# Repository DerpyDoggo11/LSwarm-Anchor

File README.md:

# LSwarm Anchor
A UWB Anchor made for the LSwarm micro drones

## 3D Preview

## Wiring

## Schematic

### Download ./latestProduction to begin fabricating the PCB

## Introduction
In an effort to make a cheaper alternative for micro drones, specifically for volumetric (3D) light displays, I designed drones that use an ultra-wide-band (UWB) module instead of an expensive gps to communicate with ground stations with UWB modules often called anchors. With three of these modules placed in a triangular formation, you can estimate the drone's specific position in 2D space. With four or more of these modules, you can precisely track the drone's position in a full 3D space. I recommend around 5 modules for more precision (also LCSC tends to offer pcbs in terms of 5 which makes this almost just as cheap), but four modules will work as well. 

I have not physically tested this device yet, but typically UWB modules can have a range of up to 100 meters or around 300 feet, which is more than enough for many applications. Also, UWB frequenceis can work through walls, but it may be less accurate or cause desyncing with the drone. 

Note: These anchors do not actively run the computations to position the drones, you must also have a dedicated ground station with wifi such as a Raspbbery PI Zero 2 W for computing.

## Bill of Materials (for 5 anchors)

| Quantity | Components | Price | Link |
|--------- |----------|----------| -----|
| 5  | 18650 Batteries | ~$33.93 (with shipping) | [here](https://liionwholesale.com/products/molicel-npe-inr-18650-m35a-10a-3500mah-flat-top-18650-battery-authorized-distributor?variant=32004772528197)
| 5 | 2.4G Wifi Antenna | ~$1.39 | select 5cm FPC-IPX4 cable from [here](https://www.aliexpress.us/item/3256802833801038.html?spm=a2g0o.productlist.main.17.44bbCrBdCrBdFl&algo_pvid=20d56933-2b0c-45d5-8601-1bc6a9682401&algo_exp_id=20d56933-2b0c-45d5-8601-1bc6a9682401-16&pdp_ext_f=%7B%22order%22%3A%221074%22%2C%22eval%22%3A%221%22%2C%22fromPage%22%3A%22search%22%7D&pdp_npi=6%40dis%21USD%213.55%213.52%21%21%213.55%213.52%21%402101ef5e17781321493642302e40a6%2112000023272348781%21sea%21US%217493938711%21X%211%210%21n_tag%3A-29913%3Bd%3A21b1ce8d%3Bm03_new_user%3A-29895&curPageLogUid=rLnZuf4b98Bi&utparam-url=scene%3Asearch%7Cquery_from%3A%7Cx_object_id%3A1005003020115790%7C_p_origin_prod%3A)
| 5  | LS Anchor PCBs | ~$10 (with shipping, cost can vary widely however) | Download repo, extract fabrication files, and fabricate through JLCPCB (complete instructions for this may come soon)
| 5  | Electrical Components for each PCB | ~$88.67 (this is on the high end, cost can vary widely) | See production BOM for a full list, the PCB fabrication files automatically include these components as well.
Total: $133.99

## Tools / Other parts:
- Hot-air reflow station or SMD hot plate
- Soldering iron + solder
- Solder paste for SMD components
- Tweezers for SMD components

For drone light displays, you'll also need the drones and a ground station.

## Assembly:
1. Apply solder paste to all smd components directly or through a stencil
2. Heat up components with a hot plate or hot-air gun
3. Solder on the battery connector and connect the battery
4. Plug in USB-C port and upload software

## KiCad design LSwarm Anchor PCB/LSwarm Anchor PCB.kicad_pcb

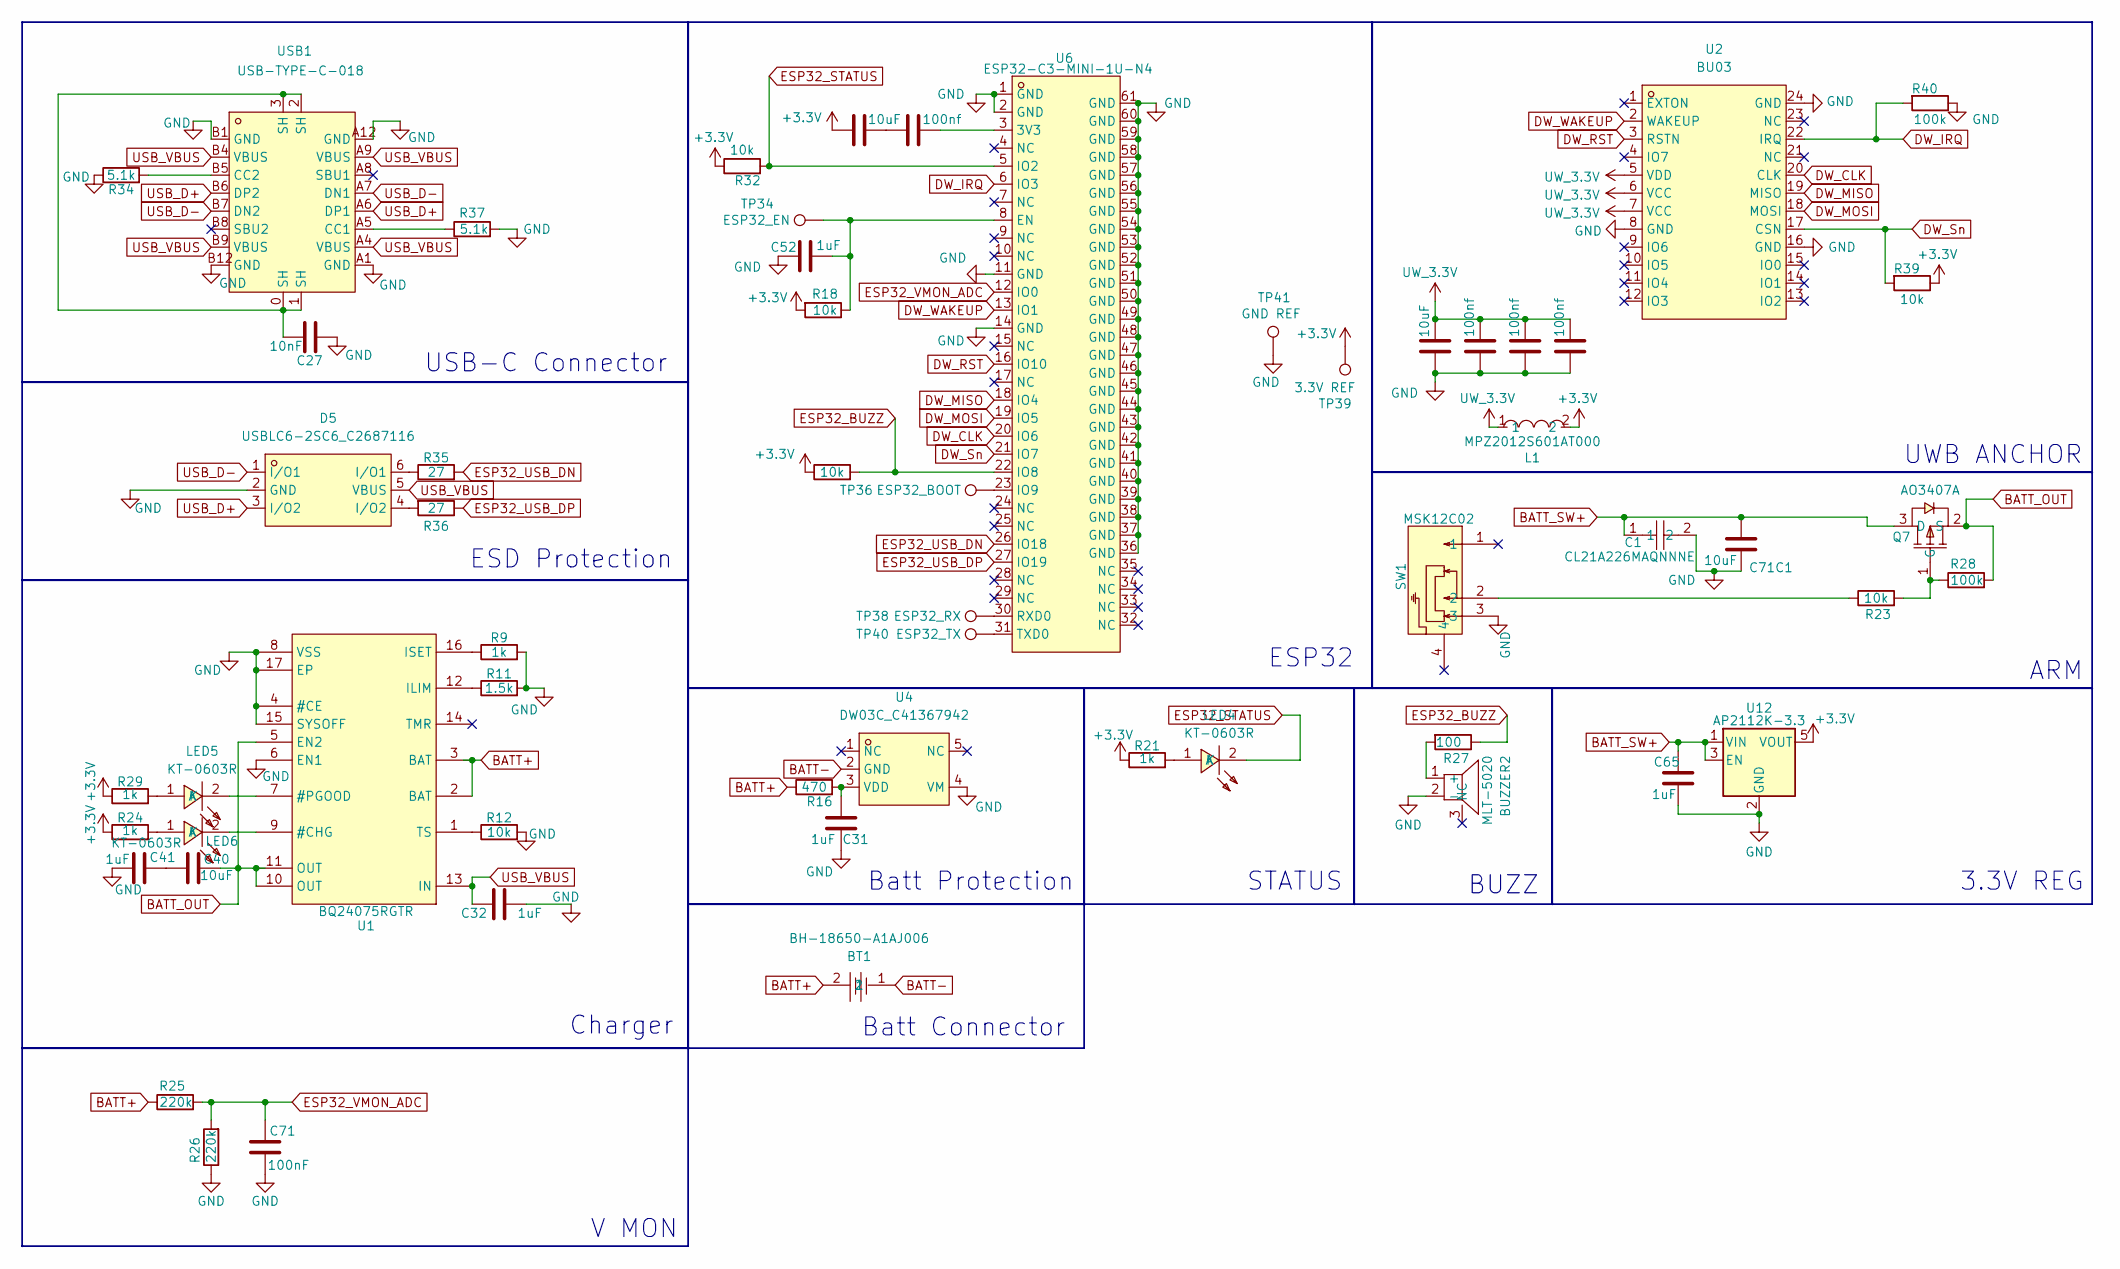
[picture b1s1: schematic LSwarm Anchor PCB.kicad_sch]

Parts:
BT1: BH-18650-A1AJ006; BAT-TH_BH-18650-A1AJ006; MPN BH-18650-A1AJ006; LCSC Part C5290175
BUZZER2: MLT-5020; BUZ-SMD_L5.0-W5.5-P4.60; MPN MLT-5020; LCSC Part C94598
C1: CL21A226MAQNNNE; C0805; MPN CL21A226MAQNNNE; LCSC Part C45783
C27: 10nF; C_0603_1608Metric
C31, C32, C41, C52, C65: 1uF; C_0603_1608Metric
C40, C55, C62: 10uF; C_0603_1608Metric
C56, C58, C59, C61: 100nf; C_0603_1608Metric
C71: 100nF; C_0603_1608Metric
C71C1: 10uF; C_0805_2012Metric
D5: USBLC6-2SC6_C2687116; SOT-23-6_L2.9-W1.6-P0.95-LS2.8-BL; MPN USBLC6-2SC6; LCSC Part C2687116
L1: MPZ2012S601AT000; L0805; MPN MPZ2012S601AT000; LCSC Part C21519
LED4, LED5, LED6: KT-0603R; LED-SMD_L1.6-W0.8-R-RD; MPN KT-0603R; LCSC Part C2286
Q7: AO3407A; SOT-23-3_L2.9-W1.6-P1.90-LS2.8-BR; MPN AO3407A; LCSC Part C15155
R9, R21, R24, R29: 1k; R_0603_1608Metric
R11: 1.5k; R_0603_1608Metric
R12, R18, R23, R32, R33, R39: 10k; R_0603_1608Metric
R16: 470; R_0603_1608Metric
R25, R26: 220k; R_0603_1608Metric
R27: 100; R_0603_1608Metric
R28, R40: 100k; R_0603_1608Metric
R34, R37: 5.1k; R_0603_1608Metric
R35, R36: 27; R_0603_1608Metric
SW1: MSK12C02; SW-TH_MSK12C02; MPN MSK12C02; LCSC Part C431540
TP34: ESP32_EN; TestPoint_Pad_1.0x1.0mm
TP36: ESP32_BOOT; TestPoint_Pad_1.0x1.0mm
TP38: ESP32_RX; TestPoint_Pad_1.0x1.0mm
TP39: 3.3V REF; TestPoint_Pad_1.0x1.0mm
TP40: ESP32_TX; TestPoint_Pad_1.0x1.0mm
TP41: GND REF; TestPoint_Pad_1.0x1.0mm
U1: BQ24075RGTR; QFN-16_L3.0-W3.0-P0.50-TL-EP1.7; MPN BQ24075RGTR; LCSC Part C15464
U2: BU03; WIRELM-SMD_BU03; MPN BU03; LCSC Part C42419011
U4: DW03C_C41367942; SOT-23-5_L2.9-W1.6-P0.95-LS2.9-BL; MPN DW03C; LCSC Part C41367942
U6: ESP32-C3-MINI-1U-N4; WIFIM-SMD_61P-L13.2-W12.5-P0.80; MPN ESP32-C3-MINI-1U-N4; LCSC Part C2911374
U12: AP2112K-3.3; SOT-23-5
USB1: USB-TYPE-C-018; USB-C_SMD-TYPE-C-31-M-12; MPN USB-TYPE-C-018; LCSC Part C2927038

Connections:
+3.3V: C55.2, L1.2, R18.2, R21.1, R24.1, R29.1, R32.1, R33.1, R39.1, TP39.1 (1_1), U12.5 (VOUT)
BATT+: BT1.2, R16.1, R25.1, U1.2 (BAT), U1.3 (BAT)
BATT-: BT1.1, U4.2 (GND)
BATT_OUT: C40.1, Q7.2 (S), R28.2, U1.5 (EN2), U1.10 (OUT), U1.11 (OUT)
BATT_SW+: C1.1, C65.2, C71C1.2, Q7.3 (D), U12.1 (VIN), U12.3 (EN)
DW_CLK: U2.20 (CLK), U6.20 (IO6)
DW_IRQ: R40.2, U2.22 (IRQ), U6.6 (IO3)
DW_MISO: U2.19 (MISO), U6.18 (IO4)
DW_MOSI: U2.18 (MOSI), U6.19 (IO5)
DW_RST: U2.3 (RSTN), U6.16 (IO10)
DW_Sn: R39.2, U2.17 (CSN), U6.21 (IO7)
DW_WAKEUP: U2.2 (WAKEUP), U6.13 (IO1)
ESP32_BUZZ: R27.1, R33.2, U6.22 (IO8)
ESP32_STATUS: LED4.2 (K), R32.2, U6.5 (IO2)
ESP32_USB_DN: R35.2, U6.26 (IO18)
ESP32_USB_DP: R36.1, U6.27 (IO19)
ESP32_VMON_ADC: C71.2, R25.2, R26.2, U6.12 (IO0)
GND: BUZZER2.2 (-), C1.2, C27.1, C31.2, C32.1, C41.1, C52.1, C58.2, C59.2, C61.2, C62.2, C65.1, C71.1, C71C1.1, D5.2 (GND), R9.2, R11.2, R12.2, R26.1, R34.1, R37.2, R40.1, SW1.3, TP41.1 (1_1), U1.4 (#CE), U1.6 (EN1), U1.8 (VSS), U1.15 (SYSOFF), U1.17 (EP), U2.8 (GND), U2.16 (GND), U2.24 (GND), U4.4 (VM), U6.1 (GND), U6.2 (GND), U6.11 (GND), U6.14 (GND), U6.36 (GND), U6.37 (GND), U6.38 (GND), U6.39 (GND), U6.40 (GND), U6.41 (GND), U6.42 (GND), U6.43 (GND), U6.44 (GND), U6.45 (GND), U6.46 (GND), U6.47 (GND), U6.48 (GND), U6.49 (GND), U6.50 (GND), U6.51 (GND), U6.52 (GND), U6.53 (GND), U6.54 (GND), U6.55 (GND), U6.56 (GND), U6.57 (GND), U6.58 (GND), U6.59 (GND), U6.60 (GND), U6.61 (GND), U12.2 (GND), USB1.A1 (GND), USB1.A12 (GND), USB1.B1 (GND), USB1.B12 (GND)
unnamed: BUZZER2.1 (+), R27.2
unnamed: C27.2, USB1.0 (SH), USB1.1 (SH), USB1.2 (SH), USB1.3 (SH)
unnamed: C40.2, C41.2
unnamed: C55.1, C56.2
unnamed: D5.6 (I/O1), R35.1
unnamed: D5.4 (I/O2), R36.2
unnamed: LED4.1 (A), R21.2
unnamed: LED5.1 (A), R29.2
unnamed: LED5.2 (K), U1.7 (#PGOOD)
unnamed: LED6.1 (A), R24.2
unnamed: LED6.2 (K), U1.9 (#CHG)
unnamed: Q7.1 (G), R23.2, R28.1
unnamed: R23.1, SW1.2
unnamed: R11.1, U1.12 (ILIM)
unnamed: R9.1, U1.16 (ISET)
unnamed: R12.1, U1.1 (TS)
unnamed: C31.1, R16.2, U4.3 (VDD)
unnamed: C56.1, U6.3 (3V3)
unnamed: C52.2, R18.1, TP34.1 (1_1), U6.8 (EN)
unnamed: TP36.1 (1_1), U6.23 (IO9)
unnamed: TP38.1 (1_1), U6.30 (RXD0)
unnamed: TP40.1 (1_1), U6.31 (TXD0)
unnamed: R37.1, USB1.A5 (CC1)
unnamed: R34.2, USB1.B5 (CC2)
USB_D+: D5.3 (I/O2), USB1.A6 (DP1), USB1.B6 (DP2)
USB_D-: D5.1 (I/O1), USB1.A7 (DN1), USB1.B7 (DN2)
USB_VBUS: C32.2, D5.5 (VBUS), U1.13 (IN), USB1.A4 (VBUS), USB1.A9 (VBUS), USB1.B4 (VBUS), USB1.B9 (VBUS)
UW_3.3V: C58.1, C59.1, C61.1, C62.1, L1.1, U2.5 (VDD), U2.6 (VCC), U2.7 (VCC)

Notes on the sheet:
USB-C Connector
Batt Connector
BUZZ
V MON
STATUS
UWB ANCHOR
ESP32
3.3V REG
ARM
Batt Protection
Charger
ESD Protection

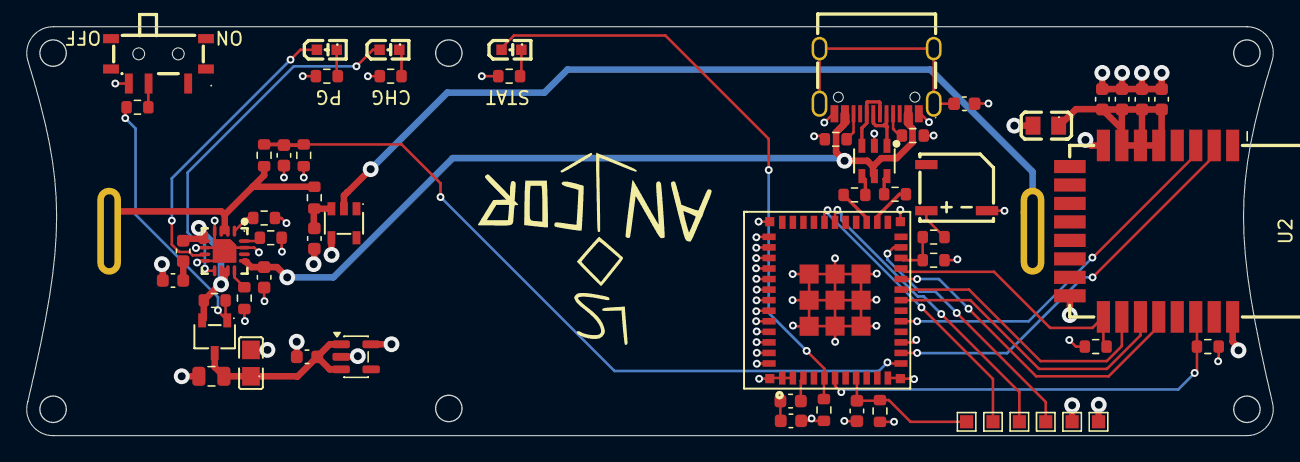
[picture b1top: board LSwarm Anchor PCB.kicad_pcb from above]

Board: 4 copper layers, 94.5 x 31.0 mm, 58 parts (1 on the bottom side), 46 nets.

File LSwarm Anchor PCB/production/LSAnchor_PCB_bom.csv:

Designator,Footprint,Quantity,Value,LCSC Part #
BT1,BAT-TH_BH-18650-A1AJ006,1,BH-18650-A1AJ006,C5290175
BUZZER2,BUZ-SMD_L5.0-W5.5-P4.60,1,MLT-5020,C94598
C1,C0805,1,CL21A226MAQNNNE,C45783
C27,0603,1,10nF,
"C31, C32, C41, C52, C65",0603,5,1uF,
"C40, C55, C62",0603,3,10uF,
"C56, C58, C59, C61, C71",0603,5,100nf,
C71C1,0805,1,10uF,
"D4, D7, D8",0402,3,LED,
D5,SOT-23-6_L2.9-W1.6-P0.95-LS2.8-BL,1,USBLC6-2SC6_C2687116,C2687116
L1,L0805,1,MPZ2012S601AT000,C21519
Q7,SOT-23-3_L2.9-W1.6-P1.90-LS2.8-BR,1,AO3407A,C15155
R11,0603,1,1.5k,
"R12, R18, R23, R32, R33, R39",0603,6,10k,
R16,0603,1,470,
"R21, R24, R29, R9",0603,4,1k,
"R25, R26",0603,2,220k,
R27,0603,1,100,
"R28, R40",0603,2,100k,
"R34, R37",0603,2,5.1k,
"R35, R36",0603,2,27,
SW1,SW-TH_MSK12C02,1,MSK12C02,C431540
TP34,TestPoint_Pad_1.0x1.0mm,1,ESP32_EN,
TP36,TestPoint_Pad_1.0x1.0mm,1,ESP32_BOOT,
TP38,TestPoint_Pad_1.0x1.0mm,1,ESP32_RX,
TP39,TestPoint_Pad_1.0x1.0mm,1,3.3V REF,
TP40,TestPoint_Pad_1.0x1.0mm,1,ESP32_TX,
TP41,TestPoint_Pad_1.0x1.0mm,1,GND REF,
U1,QFN-16_L3.0-W3.0-P0.50-TL-EP1.7,1,BQ24075RGTR,C15464
U12,SOT-23-5,1,AP2112K-3.3,
U2,WIRELM-SMD_BU03,1,BU03,C42419011
U4,SOT-23-5_L2.9-W1.6-P0.95-LS2.9-BL,1,DW03C_C41367942,C41367942
U6,WIFIM-SMD_61P-L13.2-W12.5-P0.80,1,ESP32-C3-MINI-1U-N4,C2911374
USB1,USB-C_SMD-TYPE-C-31-M-12,1,USB-TYPE-C-018,C2927038

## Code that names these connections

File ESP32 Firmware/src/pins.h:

#pragma once
#include <Arduino.h>


static constexpr int PIN_DW_WAKEUP = 1;
static constexpr int PIN_DW_IRQ    = 3;
static constexpr int PIN_DW_MISO   = 4;
static constexpr int PIN_DW_MOSI   = 5;
static constexpr int PIN_DW_CLK    = 6;
static constexpr int PIN_DW_CS     = 7;
static constexpr int PIN_DW_RST    = 10;

// HMI
static constexpr int PIN_STATUS_LED = 2; 
static constexpr int PIN_BUZZER = 21;

#define STATUS_LED_ACTIVE_LOW 1

// Power
static constexpr int   PIN_VMON_ADC = 0;
static constexpr float VBAT_DIVIDER = 2.0f;

static constexpr float VBAT_FULL     = 4.10f;
static constexpr float VBAT_WARN     = 3.40f;
static constexpr float VBAT_CRITICAL = 3.10f;
